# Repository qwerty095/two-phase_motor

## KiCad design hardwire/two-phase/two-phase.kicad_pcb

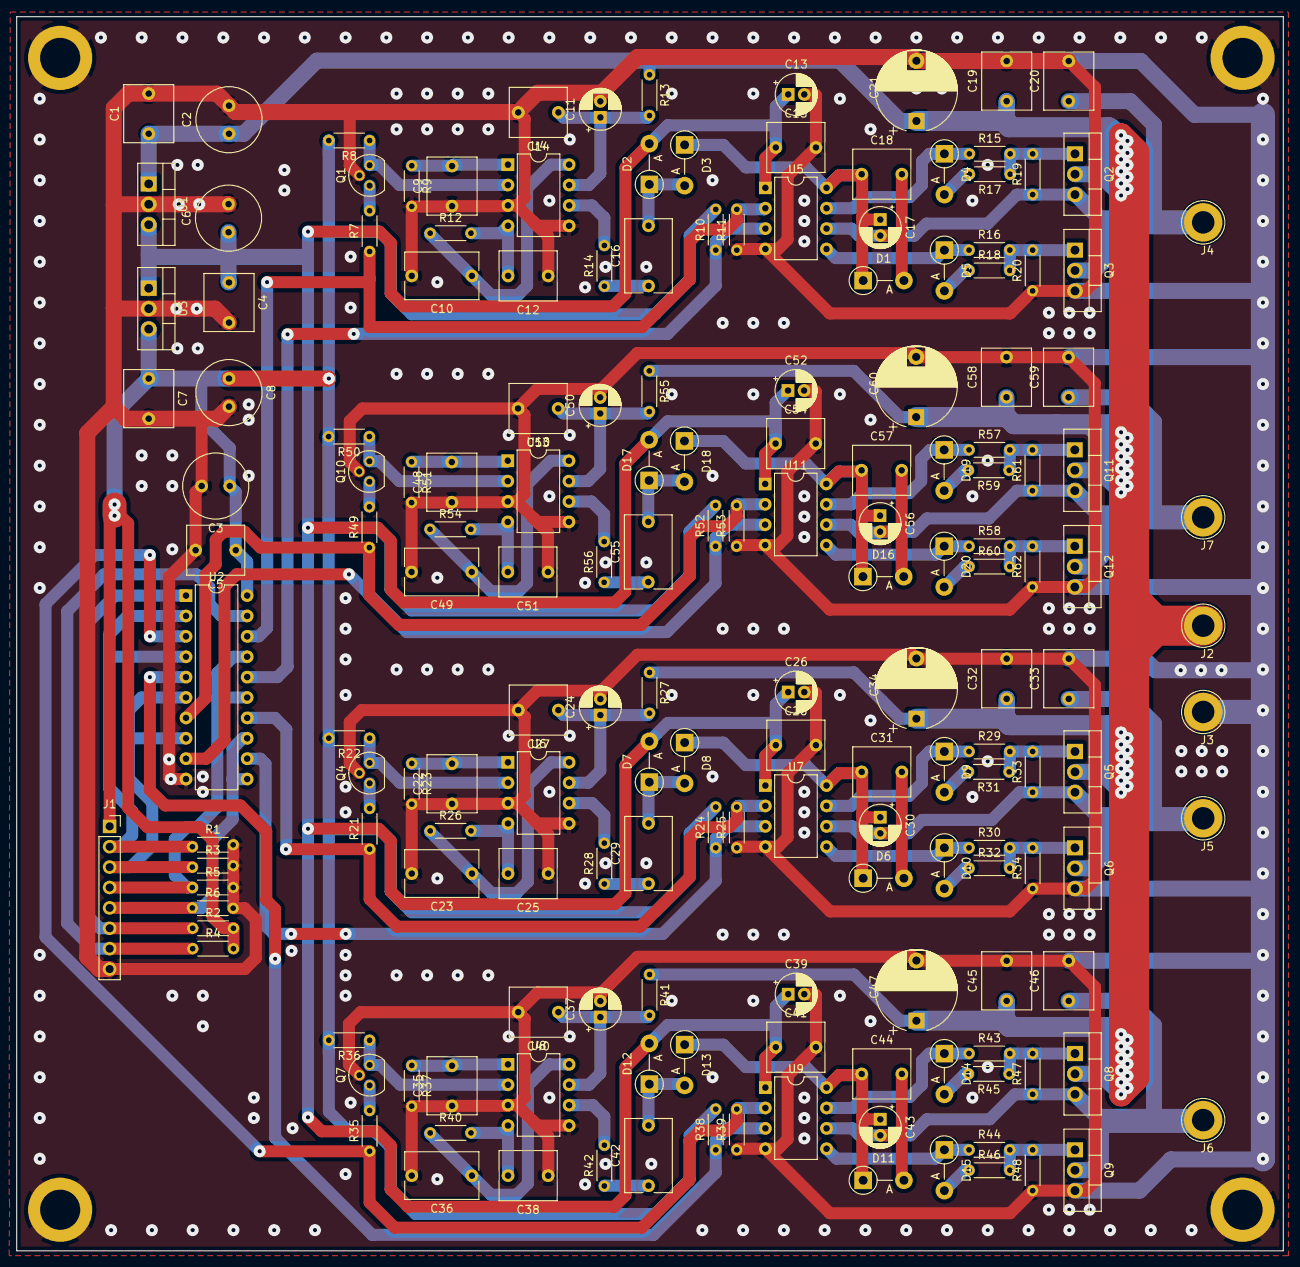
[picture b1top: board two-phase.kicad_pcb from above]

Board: 2 copper layers, 157.8 x 153.8 mm, 172 parts (0 on the bottom side), 86 nets.

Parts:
C1, C4, C5, C7, C14, C15, C19, C27, C28, C32, C40, C41, C45, C53, C54, C58: 100n; C_Rect_L7.0mm_W6.0mm_P5.00mm
C2, C3, C6, C8: 22u; C_Radial_D8.0mm_H11.5mm_P3.50mm
C9, C20, C22, C33, C35, C46, C48, C59: 1n; C_Rect_L7.0mm_W6.0mm_P5.00mm
C10, C16, C23, C29, C36, C42, C49, C55: 1u; C_Rect_L9.0mm_W5.7mm_P7.50mm_MKT
C11, C13, C17, C24, C26, C30, C37, C39, C43, C50, C52, C56: 10u; CP_Radial_D5.0mm_P2.00mm
C12, C18, C25, C31, C38, C44, C51, C57: 10n; C_Rect_L7.0mm_W6.0mm_P5.00mm
C21, C34, C47, C60: 220u; CP_Radial_D10.0mm_P7.50mm
D1, D6, D11, D16: 1N4744A; D_DO-41_SOD81_P5.08mm_Vertical_AnodeUp
D2, D3, D7, D8, D12, D13, D17, D18: 1n4007; D_DO-41_SOD81_P5.08mm_Vertical_AnodeUp
D4, D5, D9, D10, D14, D15, D19, D20: 1N4007; D_DO-41_SOD81_P5.08mm_Vertical_AnodeUp
J1: Conn_01x08_Female; PinSocket_1x08_P2.54mm_Vertical
J2, J3, J4, J5, J6, J7: Conn_01x01_Female; TestPoint_Loop_D3.80mm_Drill2.8mm
Q1, Q4, Q7, Q10: BC849; TO-92
Q2, Q3, Q5, Q6, Q8, Q9, Q11, Q12: IRF3205; TO-220-3_Vertical
R1, R2, R3, R4, R5, R6, R7, R8, R10, R11, R19, R20, R21, R22, R24, R25, R33, R34, R35, R36, R38, R39, R47, R48, R49, R50, R52, R53, R61, R62: 10k; R_Axial_DIN0204_L3.6mm_D1.6mm_P5.08mm_Horizontal
R9, R12, R23, R26, R37, R40, R51, R54: 100k; R_Axial_DIN0204_L3.6mm_D1.6mm_P5.08mm_Horizontal
R13, R14, R15, R16, R17, R18, R27, R28, R29, R30, R31, R32, R41, R42, R43, R44, R45, R46, R55, R56, R57, R58, R59, R60: 10; R_Axial_DIN0204_L3.6mm_D1.6mm_P5.08mm_Horizontal
U1: LM7812_TO220; TO-220-3_Vertical
U2: 74HC244; DIP-20_W7.62mm
U3: LM7805_TO220; TO-220-3_Vertical
U4, U6, U8, U10: UC2845_SOIC8; DIP-8_W7.62mm
U5, U7, U9, U11: IRS2003; DIP-8_W7.62mm

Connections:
+5V: C3.1, C5.1, C7.1, C8.1, J1.1, R2.2, R4.2, R8.2, R10.2, R22.2, R24.2, R36.2, R38.2, R50.2, R52.2, U2.20 (VCC), U3.3 (VO)
+12V: C4.1, C6.1, C13.1, C15.1, C26.1, C28.1, C39.1, C41.1, C52.1, C54.1, D2.2 (A), D7.2 (A), D12.2 (A), D17.2 (A), U1.3 (VO), U3.1 (VI), U5.1 (VCC), U7.1 (VCC), U9.1 (VCC), U11.1 (VCC)
+24V: C1.1, C2.1, C19.1, C21.1, C32.1, C34.1, C45.1, C47.1, C58.1, C60.1, J2.1, Q2.2 (D), Q5.2 (D), Q8.2 (D), Q11.2 (D), R13.1, R27.1, R41.1, R55.1, U1.1 (VI)
/DIR_OR_PWM_PH_1_B: J1.3, R3.1, U2.6 (1A2), U2.8 (1A3)
/DIR_OR_PWM_PH_2_B: J1.5, R6.1, U2.11 (2A3), U2.13 (2A2)
/DIR_PH_1_A: J1.2, R1.1, U2.2 (1A0), U2.4 (1A1)
/DIR_PH_2_A: J1.4, R5.1, U2.15 (2A1), U2.17 (2A0)
/DRIVER_1/33-35V_on_active: C17.1, C18.1, D1.1 (K), D3.1 (K), U5.8 (VB)
/DRIVER_2/33-35V_on_active: C30.1, C31.1, D6.1 (K), D8.1 (K), U7.8 (VB)
/DRIVER_3/33-35V_on_active: C43.1, C44.1, D11.1 (K), D13.1 (K), U9.8 (VB)
/DRIVER_4/33-35V_on_active: C56.1, C57.1, D16.1 (K), D18.1 (K), U11.8 (VB)
/M_1_HI: R7.1, R11.2, U2.18 (1Y0), U5.2 (HIN)
/M_1_LO: R10.1, U2.16 (1Y1), U5.3 (~LIN)
/M_2_HI: R21.1, R25.2, U2.14 (1Y2), U7.2 (HIN)
/M_2_LO: R24.1, U2.12 (1Y3), U7.3 (~LIN)
/M_3_HI: R35.1, R39.2, U2.3 (2Y0), U9.2 (HIN)
/M_3_LO: R38.1, U2.5 (2Y1), U9.3 (~LIN)
/M_4_HI: R49.1, R53.2, U2.7 (2Y2), U11.2 (HIN)
/M_4_LO: R52.1, U2.9 (2Y3), U11.3 (~LIN)
/OUT_PH_1_A: C17.2, C18.2, C20.1, D1.2 (A), J4.1, Q2.3 (S), Q3.2 (D), R19.1, U5.6 (VS)
/OUT_PH_1_B: C30.2, C31.2, C33.1, D6.2 (A), J5.1, Q5.3 (S), Q6.2 (D), R33.1, U7.6 (VS)
/OUT_PH_2_A: C43.2, C44.2, C46.1, D11.2 (A), J6.1, Q8.3 (S), Q9.2 (D), R47.1, U9.6 (VS)
/OUT_PH_2_B: C56.2, C57.2, C59.1, D16.2 (A), J7.1, Q11.3 (S), Q12.2 (D), R61.1, U11.6 (VS)
/~EN_PH_1: J1.6, R2.1, U2.1 (1OE)
/~EN_PH_2: J1.7, R4.1, U2.19 (2OE)
GND: C1.2, C2.2, C3.2, C4.2, C5.2, C6.2, C7.2, C8.2, C9.1, C10.2, C11.2, C12.1, C13.2, C14.2, C15.2, C19.2, C20.2, C21.2, C22.1, C23.2, C24.2, C25.1, C26.2, C27.2, C28.2, C32.2, C33.2, C34.2, C35.1, C36.2, C37.2, C38.1, C39.2, C40.2, C41.2, C45.2, C46.2, C47.2, C48.1, C49.2, C50.2, C51.1, C52.2, C53.2, C54.2, C58.2, C59.2, C60.2, J1.8, J3.1, Q1.2 (E), Q3.3 (S), Q4.2 (E), Q6.3 (S), Q7.2 (E), Q9.3 (S), Q10.2 (E), Q12.3 (S), R1.2, R3.2, R5.2, R6.2, R9.2, R11.1, R20.1, R23.2, R25.1, R34.1, R37.2, R39.1, R48.1, R51.2, R53.1, R62.1, U1.2 (GND), U2.10 (GND), U3.2 (GND), U4.3 (CS), U4.5 (GND), U5.4 (COM), U6.3 (CS), U6.5 (GND), U7.4 (COM), U8.3 (CS), U8.5 (GND), U9.4 (COM), U10.3 (CS), U10.5 (GND), U11.4 (COM)
unnamed: C9.2, R9.1, U4.1 (COMP)
unnamed: C10.1, R12.1, U4.8 (VREF)
unnamed: C11.1, C14.1, R13.2, U4.7 (VCC)
unnamed: C12.2, R12.2, U4.4 (RC)
unnamed: C16.1, R14.1
unnamed: C16.2, D2.1 (K), D3.2 (A)
unnamed: C22.2, R23.1, U6.1 (COMP)
unnamed: C23.1, R26.1, U6.8 (VREF)
unnamed: C24.1, C27.1, R27.2, U6.7 (VCC)
unnamed: C25.2, R26.2, U6.4 (RC)
unnamed: C29.1, R28.1
unnamed: C29.2, D7.1 (K), D8.2 (A)
unnamed: C35.2, R37.1, U8.1 (COMP)
unnamed: C36.1, R40.1, U8.8 (VREF)
unnamed: C37.1, C40.1, R41.2, U8.7 (VCC)
unnamed: C38.2, R40.2, U8.4 (RC)
unnamed: C42.1, R42.1
unnamed: C42.2, D12.1 (K), D13.2 (A)
unnamed: C48.2, R51.1, U10.1 (COMP)
unnamed: C49.1, R54.1, U10.8 (VREF)
unnamed: C50.1, C53.1, R55.2, U10.7 (VCC)
unnamed: C51.2, R54.2, U10.4 (RC)
unnamed: C55.1, R56.1
unnamed: C55.2, D17.1 (K), D18.2 (A)
unnamed: D4.1 (K), R15.1, U5.7 (HO)
unnamed: D4.2 (A), R17.2
unnamed: D5.1 (K), R16.1, U5.5 (LO)
unnamed: D5.2 (A), R18.1
unnamed: D9.1 (K), R29.1, U7.7 (HO)
unnamed: D9.2 (A), R31.2
unnamed: D10.1 (K), R30.1, U7.5 (LO)
unnamed: D10.2 (A), R32.1
unnamed: D14.1 (K), R43.1, U9.7 (HO)
unnamed: D14.2 (A), R45.2
unnamed: D15.1 (K), R44.1, U9.5 (LO)
unnamed: D15.2 (A), R46.1
unnamed: D19.1 (K), R57.1, U11.7 (HO)
unnamed: D19.2 (A), R59.2
unnamed: D20.1 (K), R58.1, U11.5 (LO)
unnamed: D20.2 (A), R60.1
unnamed: Q1.1 (B), R7.2
unnamed: Q1.3 (C), R8.1, U4.2 (FB)
unnamed: Q3.1 (G), R16.2, R18.2, R20.2
unnamed: Q4.1 (B), R21.2
unnamed: Q4.3 (C), R22.1, U6.2 (FB)
unnamed: Q6.1 (G), R30.2, R32.2, R34.2
unnamed: Q7.1 (B), R35.2
unnamed: Q7.3 (C), R36.1, U8.2 (FB)
unnamed: Q9.1 (G), R44.2, R46.2, R48.2
unnamed: Q10.1 (B), R49.2
unnamed: Q10.3 (C), R50.1, U10.2 (FB)
unnamed: Q12.1 (G), R58.2, R60.2, R62.2
unnamed: R14.2, U4.6 (OUT)
unnamed: Q2.1 (G), R15.2, R17.1, R19.2
unnamed: R28.2, U6.6 (OUT)
unnamed: Q5.1 (G), R29.2, R31.1, R33.2
unnamed: R42.2, U8.6 (OUT)
unnamed: Q8.1 (G), R43.2, R45.1, R47.2
unnamed: R56.2, U10.6 (OUT)
unnamed: Q11.1 (G), R57.2, R59.1, R61.2

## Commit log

2023-02-13 hardwire
2023-02-13 softwire
2023-03-09 hardwire updete
2023-03-10 update pcb, generate gerber
